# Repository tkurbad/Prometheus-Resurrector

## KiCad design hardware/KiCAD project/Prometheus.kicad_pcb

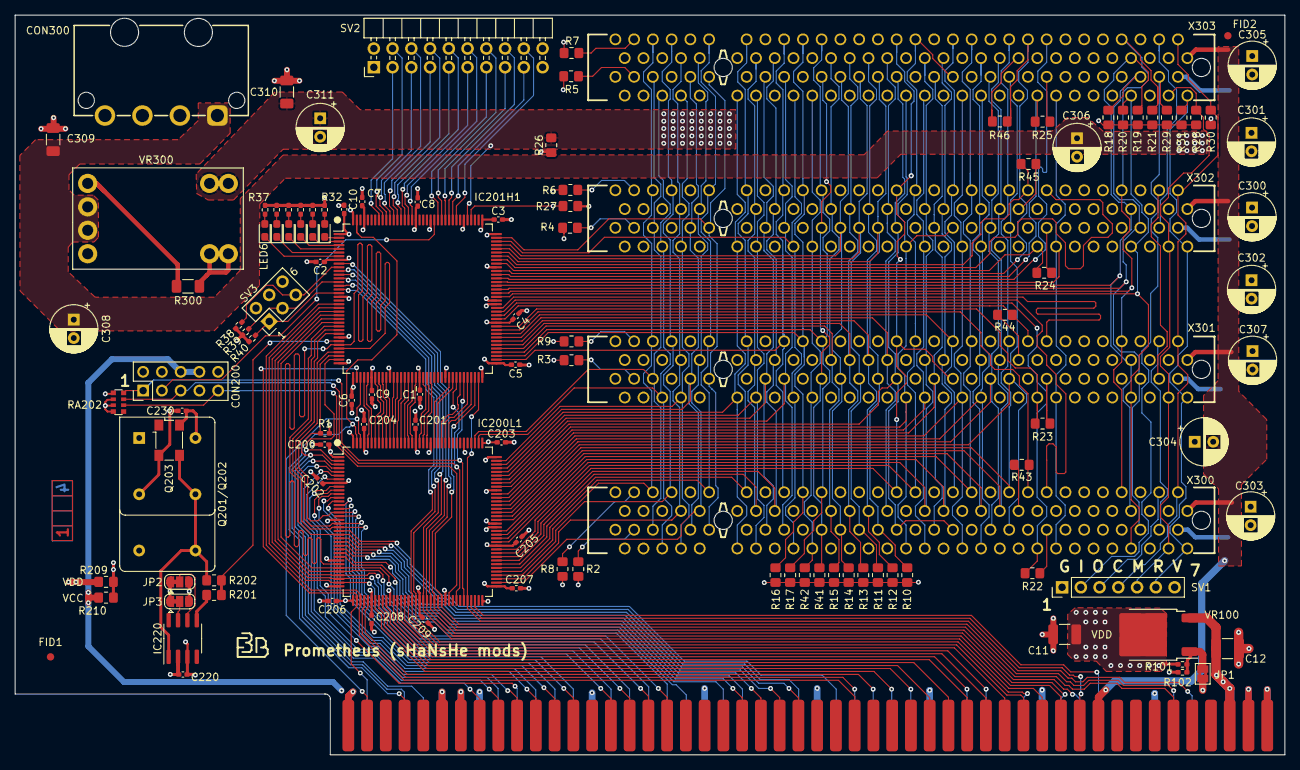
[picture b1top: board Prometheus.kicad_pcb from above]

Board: 4 copper layers, 172.0 x 100.2 mm, 118 parts (0 on the bottom side), 208 nets.

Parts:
C1, C2, C3, C4, C5, C6, C7, C8, C9, C10, C200, C201, C202, C203, C204, C205, C206, C207, C208, C209, C220, C230: 100nF; C_0402_1005Metric_Pad0.74x0.62mm_HandSolder
C11, C12: 10uF Tantalum; C_1210_3225Metric_Pad1.33x2.70mm_HandSolder
C300, C301, C302, C303, C304, C305, C306, C307, C308, C311: 100uF; CP_Radial_D6.3mm_P2.50mm
C309, C310: 100nF; C_1206_3216Metric_Pad1.33x1.80mm_HandSolder
CON200: Conn_02x05_Odd_Even; PinHeader_2x05_P2.54mm_Vertical
CON300: Conn_01x04_Pin; TE-350211-MATE-N-LCK-RightAngle
FID1, FID2: Fiducial; Fiducial_1mm_Mask2mm
IC200L1, IC201H1: XC95144XL-TQ144; TQFP-144_20x20mm_P0.5mm
IC220: NB3N502; SOIC-8_3.9x4.9mm_P1.27mm
JP1: SolderJumper_2_Bridged; SolderJumper-2_P1.3mm_Bridged2Bar_Pad1.0x1.5mm
JP2, JP3: SolderJumper_3_Bridged12; SolderJumper-3_P1.3mm_Bridged12_RoundedPad1.0x1.5mm
LED1, LED2, LED3, LED4, LED5, LED6: LED; LED_0603_1608Metric_Pad1.05x0.95mm_HandSolder
Q201/Q202: 33MHz; Oscillator_DIP-14_DIP-8
Q203: 33MHz; Oscillator_SMD_Fordahl_DFAS15-4Pin_5.0x3.2mm
R1, R38, R39, R40: 4k7; R_0402_1005Metric_Pad0.72x0.64mm_HandSolder
R2, R3, R4, R5, R6, R7, R8, R9, R10, R11, R12, R13, R14, R15, R16, R17, R18, R19, R20, R21, R22, R23, R24, R25, R28, R29, R30, R31, R41, R42: 1k0; R_0805_2012Metric_Pad1.20x1.40mm_HandSolder
R26: 3k3; R_0805_2012Metric_Pad1.20x1.40mm_HandSolder
R27: 4k7; R_0805_2012Metric_Pad1.20x1.40mm_HandSolder
R32, R33, R34, R35, R36, R37: 680; R_0402_1005Metric_Pad0.72x0.64mm_HandSolder
R43, R44, R45, R46: 10k0; R_0805_2012Metric_Pad1.20x1.40mm_HandSolder
R101: 150; R_0402_1005Metric_Pad0.72x0.64mm_HandSolder
R102: 240; R_0402_1005Metric_Pad0.72x0.64mm_HandSolder
R201, R202: 15R; R_0805_2012Metric_Pad1.20x1.40mm_HandSolder
R209, R210: FerriteBead_Small; R_0805_2012Metric_Pad1.20x1.40mm_HandSolder
R300: 2k0; R_1206_3216Metric_Pad1.30x1.75mm_HandSolder
RA202: R_Pack04; R_Array_Convex_4x0612
SV1: Conn_01x07_Pin; PinHeader_1x07_P2.54mm_Vertical
SV2: Conn_02x10_Odd_Even; PinHeader_2x10_P2.54mm_Horizontal
SV3: Conn_02x03_Odd_Even; PinHeader_2x03_P2.54mm_Vertical
U1: Zorro3
VR100: AP1117-ADJ; TO-252-2
VR300: DCDC
X300, X301, X302, X303: Bus_PCI_32bit_5V; PCI

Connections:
+3V3: C310.1, C311.1, IC201H1.113, R26.2, VR300.6 (VOUT), X300.A21 (+3.3V), X300.A27 (+3.3V), X300.A33 (+3.3V), X300.A39 (+3.3V), X300.A45 (+3.3V), X300.A53 (+3.3V), X300.B25 (+3.3V), X300.B31 (+3.3V), X300.B36 (+3.3V), X300.B41 (+3.3V), X300.B43 (+3.3V), X300.B54 (+3.3V), X301.A21 (+3.3V), X301.A27 (+3.3V), X301.A33 (+3.3V), X301.A39 (+3.3V), X301.A45 (+3.3V), X301.A53 (+3.3V), X301.B25 (+3.3V), X301.B31 (+3.3V), X301.B36 (+3.3V), X301.B41 (+3.3V), X301.B43 (+3.3V), X301.B54 (+3.3V), X302.A21 (+3.3V), X302.A27 (+3.3V), X302.A33 (+3.3V), X302.A39 (+3.3V), X302.A45 (+3.3V), X302.A53 (+3.3V), X302.B25 (+3.3V), X302.B31 (+3.3V), X302.B36 (+3.3V), X302.B41 (+3.3V), X302.B43 (+3.3V), X302.B54 (+3.3V), X303.A21 (+3.3V), X303.A27 (+3.3V), X303.A33 (+3.3V), X303.A39 (+3.3V), X303.A45 (+3.3V), X303.A53 (+3.3V), X303.B25 (+3.3V), X303.B31 (+3.3V), X303.B36 (+3.3V), X303.B41 (+3.3V), X303.B43 (+3.3V), X303.B54 (+3.3V)
+5V: C300.1, C303.1, C305.1, C307.1, CON300.4, IC201H1.112, R2.1, R3.1, R4.1, R5.1, R6.2, R7.2, R8.2, R9.2, R10.2, R11.2, R12.2, R13.2, R14.2, R15.2, R16.2, R17.2, R18.2, R19.2, R20.2, R21.2, R22.2, R23.2, R24.2, R25.2, R27.2, R28.2, R29.2, R31.2, R41.2, R42.2, R43.2, R44.2, R45.2, R46.2, SV1.7, X300.A5 (+5V), X300.A8 (+5V), X300.A10 (+5V), X300.A16 (+5V), X300.A59 (+5V), X300.A61 (+5V), X300.A62 (+5V), X300.B5 (+5V), X300.B6 (+5V), X300.B19 (+5V), X300.B59 (+5V), X300.B61 (+5V), X300.B62 (+5V), X301.A5 (+5V), X301.A8 (+5V), X301.A10 (+5V), X301.A16 (+5V), X301.A59 (+5V), X301.A61 (+5V), X301.A62 (+5V), X301.B5 (+5V), X301.B6 (+5V), X301.B19 (+5V), X301.B59 (+5V), X301.B61 (+5V), X301.B62 (+5V), X302.A5 (+5V), X302.A8 (+5V), X302.A10 (+5V), X302.A16 (+5V), X302.A59 (+5V), X302.A61 (+5V), X302.A62 (+5V), X302.B5 (+5V), X302.B6 (+5V), X302.B19 (+5V), X302.B59 (+5V), X302.B61 (+5V), X302.B62 (+5V), X303.A5 (+5V), X303.A8 (+5V), X303.A10 (+5V), X303.A16 (+5V), X303.A59 (+5V), X303.A61 (+5V), X303.A62 (+5V), X303.B5 (+5V), X303.B6 (+5V), X303.B19 (+5V), X303.B59 (+5V), X303.B61 (+5V), X303.B62 (+5V)
+12V: C301.1, C302.1, C306.1, C308.1, C309.1, CON300.1, VR300.2 (TRACK), VR300.3 (VIN), X300.A2 (+12V), X301.A2 (+12V), X302.A2 (+12V), X303.A2 (+12V)
-12V: C304.2, U1.20 (-12VDC), X300.B1 (-12V), X301.B1 (-12V), X302.B1 (-12V), X303.B1 (-12V)
AD8: IC200L1.52, U1.30 (AD8)
AD9: IC200L1.50, U1.32 (AD9)
AD10: IC200L1.48, U1.34 (AD10)
AD11: IC200L1.46, U1.36 (AD11)
AD12: IC200L1.45, U1.38 (AD12)
AD13: IC200L1.44, U1.39 (AD13)
AD14: IC200L1.43, U1.41 (AD14)
AD15: IC200L1.41, U1.43 (AD15)
AD16: IC200L1.40, U1.45 (AD16)
AD17: IC200L1.21, U1.47 (AD17)
AD18: IC200L1.23, U1.52 (AD18)
AD19: IC200L1.24, U1.54 (AD19)
AD20: IC200L1.25, U1.56 (AD20)
AD21: IC200L1.27, U1.58 (AD21)
AD22: IC200L1.26, U1.57 (AD22)
AD23: IC200L1.28, U1.59 (AD23)
AD24: IC200L1.10, U1.80 (AD24)
AD25: IC200L1.12, U1.78 (AD25)
AD26: IC200L1.14, U1.76 (AD26)
AD27: IC200L1.17, U1.71 (AD27)
AD28: IC200L1.20, IC201H1.27, U1.69 (AD28)
AD29: IC200L1.34, IC201H1.22, U1.67 (AD29)
AD30: IC200L1.32 (I/O/GCK2), IC201H1.24, U1.65 (AD30)
AD31: IC200L1.31, IC201H1.25, U1.63 (AD31)
DEBUG0: IC201H1.116, SV2.18
DEBUG1: IC201H1.117, SV2.17
DEBUG2: IC201H1.118, SV2.16
DEBUG3: IC201H1.119, SV2.15
DEBUG4: IC201H1.120, SV2.14
DEBUG5: IC201H1.121, SV2.13
DEBUG6: IC201H1.128, SV2.12
DEBUG7: IC201H1.129, SV2.11
DEBUG8: IC201H1.130, SV2.10
DEBUG9: IC201H1.131, SV2.9
DEBUG10: IC201H1.132, SV2.8
DEBUG11: IC201H1.133, SV2.7
DEBUG12: IC201H1.134, SV2.6
DEBUG13: IC201H1.135, SV2.5
DEBUG14: IC201H1.136, SV2.4
DEBUG15: IC201H1.137, SV2.3
DOE: IC200L1.2 (I/O/GTS3), IC201H1.35, U1.93 (DOE)
FC0: IC200L1.51, U1.31 (FC0)
FC1: IC200L1.49, U1.33 (FC1)
GNDD: C1.2, C2.2, C3.2, C4.2, C5.2, C6.2, C7.2, C8.2, C9.2, C10.2, C11.2, C12.2, C200.2, C201.2, C202.2, C203.2, C204.2, C205.2, C206.2, C207.2, C208.2, C209.2, C220.2, C230.2, C300.2, C301.2, C302.2, C303.2, C304.1, C305.2, C306.2, C307.2, C308.2, C309.2, C310.2, C311.2, CON200.2, CON200.10, CON300.2, CON300.3, IC200L1.18 (GND), IC200L1.29 (GND), IC200L1.36 (GND), IC200L1.47 (GND), IC200L1.62 (GND), IC200L1.72 (GND), IC200L1.89 (GND), IC200L1.90 (GND), IC200L1.99 (GND), IC200L1.108 (GND), IC200L1.114 (GND), IC200L1.123 (GND), IC200L1.144 (GND), IC201H1.18 (GND), IC201H1.29 (GND), IC201H1.36 (GND), IC201H1.47 (GND), IC201H1.62 (GND), IC201H1.72 (GND), IC201H1.89 (GND), IC201H1.90 (GND), IC201H1.99 (GND), IC201H1.108 (GND), IC201H1.114 (GND), IC201H1.123 (GND), IC201H1.144 (GND), IC220.3 (GND), JP1.2 (B), JP2.1 (A), JP3.1 (A), Q201/Q202.4 (GND), Q201/Q202.7 (GND), Q203.2 (GND), R26.1, R27.1, R30.2, R102.2, R300.1, RA202.1 (R1.1), SV1.1, SV2.1, SV2.2, SV2.19, SV2.20, SV3.2, SV3.4, SV3.6, U1.1 (GND), U1.2 (GND), U1.3 (GND), U1.4 (GND), U1.13 (GND), U1.25 (GND), U1.37 (GND), U1.49 (GND), U1.61 (GND), U1.73 (GND), U1.85 (GND), U1.87 (GND), U1.88 (GND), U1.89 (GND), U1.90 (GND), U1.99 (GND), U1.100 (GND), VR300.1 (GND), X300.A12 (GND), X300.A13 (GND), X300.A18 (GND), X300.A24 (GND), X300.A30 (GND), X300.A35 (GND), X300.A37 (GND), X300.A42 (GND), X300.A48 (GND), X300.A56 (GND), X300.B3 (GND), X300.B12 (GND), X300.B13 (GND), X300.B15 (GND), X300.B17 (GND), X300.B22 (GND), X300.B28 (GND), X300.B34 (GND), X300.B38 (GND), X300.B46 (GND), X300.B49 (GND), X300.B57 (GND), X301.A12 (GND), X301.A13 (GND), X301.A18 (GND), X301.A24 (GND), X301.A30 (GND), X301.A35 (GND), X301.A37 (GND), X301.A42 (GND), X301.A48 (GND), X301.A56 (GND), X301.B3 (GND), X301.B12 (GND), X301.B13 (GND), X301.B15 (GND), X301.B17 (GND), X301.B22 (GND), X301.B28 (GND), X301.B34 (GND), X301.B38 (GND), X301.B46 (GND), X301.B49 (GND), X301.B57 (GND), X302.A12 (GND), X302.A13 (GND), X302.A18 (GND), X302.A24 (GND), X302.A30 (GND), X302.A35 (GND), X302.A37 (GND), X302.A42 (GND), X302.A48 (GND), X302.A56 (GND), X302.B3 (GND), X302.B12 (GND), X302.B13 (GND), X302.B15 (GND), X302.B17 (GND), X302.B22 (GND), X302.B28 (GND), X302.B34 (GND), X302.B38 (GND), X302.B46 (GND), X302.B49 (GND), X302.B57 (GND), X303.A12 (GND), X303.A13 (GND), X303.A18 (GND), X303.A24 (GND), X303.A30 (GND), X303.A35 (GND), X303.A37 (GND), X303.A42 (GND), X303.A48 (GND), X303.A56 (GND), X303.B3 (GND), X303.B12 (GND), X303.B13 (GND), X303.B15 (GND), X303.B17 (GND), X303.B22 (GND), X303.B28 (GND), X303.B34 (GND), X303.B38 (GND), X303.B46 (GND), X303.B49 (GND), X303.B57 (GND)
ICON0: IC200L1.140, IC201H1.40
ICON1: IC200L1.139, IC201H1.41
ICON2: IC200L1.138, IC201H1.43
ICON3: IC200L1.137, IC201H1.44
ICON4: IC200L1.136, IC201H1.45
ICON5: IC200L1.135, IC201H1.46
ICON6: IC200L1.134, IC201H1.48
ICON7: IC200L1.133, IC201H1.49
ICON8: IC200L1.132, IC201H1.50
ICON9: IC200L1.131, IC201H1.51
ICON10: IC200L1.130, IC201H1.52
ICON11: IC200L1.129, IC201H1.53
ICON12: IC200L1.128, IC201H1.54
ICON13: IC200L1.126, IC201H1.56
ICON14: IC200L1.125, IC201H1.57
ICON15: IC200L1.124, IC201H1.58
ICON16: IC200L1.121, IC201H1.64
ICON17: IC200L1.120, IC201H1.66
ICON18: IC200L1.119, IC201H1.68
ICON19: IC200L1.118, IC201H1.69
LED0: IC201H1.2 (I/O/GTS3), LED1.1 (K)
LED1: IC201H1.3 (I/O/GTS4), LED2.1 (K)
LED2: IC201H1.4, LED3.1 (K)
LED3: IC201H1.5 (I/O/GTS1), LED4.1 (K)
LED4: IC201H1.6 (I/O/GTS2), LED5.1 (K)
LED5: IC201H1.7, LED6.1 (K)
MASTERCLK: IC200L1.30 (I/O/GCK1), IC201H1.31, IC201H1.32 (I/O/GCK2)
unnamed: IC220.6 (S0), JP2.2 (C)
unnamed: IC220.7 (S1), JP3.2 (C)
unnamed: JP1.1 (A), R101.2, R102.1, VR100.1 (ADJ)
unnamed: LED1.2 (A), R32.1
unnamed: LED2.2 (A), R33.1
unnamed: LED3.2 (A), R34.1
unnamed: LED4.2 (A), R35.1
unnamed: LED5.2 (A), R36.1
unnamed: LED6.2 (A), R37.1
unnamed: R300.2, VR300.5 (VADJ)
unnamed: R8.1, X300.B60 (ACK64#)
unnamed: R2.2, X300.A60 (REQ64#)
unnamed: R9.1, X301.B60 (ACK64#)
unnamed: R3.2, X301.A60 (REQ64#)
unnamed: R6.1, X302.B60 (ACK64#)
unnamed: R4.2, X302.A60 (REQ64#)
unnamed: R7.1, X303.B60 (ACK64#)
unnamed: R5.2, X303.A60 (REQ64#)
OPT0: IC201H1.10, R38.1, SV3.5
OPT1: IC201H1.14, R39.1, SV3.3
OPT2: IC201H1.17, R40.1, SV3.1
P-AD0: IC200L1.111, X300.A58 (AD[00]), X301.A58 (AD[00]), X302.A58 (AD[00]), X303.A58 (AD[00])
P-AD1: IC200L1.77, X300.B58 (AD[01]), X301.B58 (AD[01]), X302.B58 (AD[01]), X303.B58 (AD[01])
P-AD2: IC200L1.110, X300.A57 (AD[02]), X301.A57 (AD[02]), X302.A57 (AD[02]), X303.A57 (AD[02])
P-AD3: IC200L1.76, X300.B56 (AD[03]), X301.B56 (AD[03]), X302.B56 (AD[03]), X303.B56 (AD[03])
P-AD4: IC200L1.107, X300.A55 (AD[04]), X301.A55 (AD[04]), X302.A55 (AD[04]), X303.A55 (AD[04])
P-AD5: IC200L1.75, X300.B55 (AD[05]), X301.B55 (AD[05]), X302.B55 (AD[05]), X303.B55 (AD[05])
P-AD6: IC200L1.106, X300.A54 (AD[06]), X301.A54 (AD[06]), X302.A54 (AD[06]), X303.A54 (AD[06])
P-AD7: IC200L1.74, X300.B53 (AD[07]), X301.B53 (AD[07]), X302.B53 (AD[07]), X303.B53 (AD[07])
P-AD8: IC200L1.78, X300.B52 (AD[08]), X301.B52 (AD[08]), X302.B52 (AD[08]), X303.B52 (AD[08])
P-AD9: IC200L1.105, X300.A49 (AD[09]), X301.A49 (AD[09]), X302.A49 (AD[09]), X303.A49 (AD[09])
P-AD10: IC200L1.79, X300.B48 (AD[10]), X301.B48 (AD[10]), X302.B48 (AD[10]), X303.B48 (AD[10])
P-AD11: IC200L1.104, X300.A47 (AD[11]), X301.A47 (AD[11]), X302.A47 (AD[11]), X303.A47 (AD[11])
P-AD12: IC200L1.80, X300.B47 (AD[12]), X301.B47 (AD[12]), X302.B47 (AD[12]), X303.B47 (AD[12])
P-AD13: IC200L1.103, X300.A46 (AD[13]), X301.A46 (AD[13]), X302.A46 (AD[13]), X303.A46 (AD[13])
P-AD14: IC200L1.81, X300.B45 (AD[14]), X301.B45 (AD[14]), X302.B45 (AD[14]), X303.B45 (AD[14])
P-AD15: IC200L1.102, X300.A44 (AD[15]), X301.A44 (AD[15]), X302.A44 (AD[15]), X303.A44 (AD[15])
P-AD16: IC200L1.101, X300.A26 (IDSEL), X300.A32 (AD[16]), X301.A32 (AD[16]), X302.A32 (AD[16]), X303.A32 (AD[16])
P-AD17: IC200L1.82, X300.B32 (AD[17]), X301.A26 (IDSEL), X301.B32 (AD[17]), X302.B32 (AD[17]), X303.B32 (AD[17])
P-AD18: IC200L1.100, X300.A31 (AD[18]), X301.A31 (AD[18]), X302.A26 (IDSEL), X302.A31 (AD[18]), X303.A31 (AD[18])
P-AD19: IC200L1.83, X300.B30 (AD[19]), X301.B30 (AD[19]), X302.B30 (AD[19]), X303.A26 (IDSEL), X303.B30 (AD[19])
P-AD20: IC200L1.98, X300.A29 (AD[20]), X301.A29 (AD[20]), X302.A29 (AD[20]), X303.A29 (AD[20])
P-AD21: IC200L1.85, X300.B29 (AD[21]), X301.B29 (AD[21]), X302.B29 (AD[21]), X303.B29 (AD[21])
P-AD22: IC200L1.97, X300.A28 (AD[22]), X301.A28 (AD[22]), X302.A28 (AD[22]), X303.A28 (AD[22])
P-AD23: IC200L1.86, X300.B27 (AD[23]), X301.B27 (AD[23]), X302.B27 (AD[23]), X303.B27 (AD[23])
P-AD24: IC200L1.96, X300.A25 (AD[24]), X301.A25 (AD[24]), X302.A25 (AD[24]), X303.A25 (AD[24])
P-AD25: IC200L1.87, X300.B24 (AD[25]), X301.B24 (AD[25]), X302.B24 (AD[25]), X303.B24 (AD[25])
P-AD26: IC200L1.95, X300.A23 (AD[26]), X301.A23 (AD[26]), X302.A23 (AD[26]), X303.A23 (AD[26])
P-AD27: IC200L1.88, X300.B23 (AD[27]), X301.B23 (AD[27]), X302.B23 (AD[27]), X303.B23 (AD[27])
P-AD28: IC200L1.94, X300.A22 (AD[28]), X301.A22 (AD[28]), X302.A22 (AD[28]), X303.A22 (AD[28])
P-AD29: IC200L1.91, X300.B21 (AD[29]), X301.B21 (AD[29]), X302.B21 (AD[29]), X303.B21 (AD[29])
P-AD30: IC200L1.93, X300.A20 (AD[30]), X301.A20 (AD[30]), X302.A20 (AD[30]), X303.A20 (AD[30])
P-AD31: IC200L1.92, X300.B20 (AD[31]), X301.B20 (AD[31]), X302.B20 (AD[31]), X303.B20 (AD[31])
P-CLK0: IC201H1.87, X300.B16 (CLK)
P-CLK1: IC201H1.88, X301.B16 (CLK)
P-CLK2: IC201H1.101, X302.B16 (CLK)
P-CLK3: IC201H1.96, X303.B16 (CLK)
P-PAR: IC201H1.106, X300.A43 (PAR), X301.A43 (PAR), X302.A43 (PAR), X303.A43 (PAR)
P-TCK: R30.1, SV1.4, X300.B2 (TCK), X301.B2 (TCK), X302.B2 (TCK), X303.B2 (TCK)
P-TD1: X302.A4 (TDI), X303.B4 (TDO)
P-TD2: X301.A4 (TDI), X302.B4 (TDO)
P-TD3: X300.A4 (TDI), X301.B4 (TDO)
P-TDI: R29.1, SV1.2, X303.A4 (TDI)
P-TDO: SV1.3, X300.B4 (TDO)
P-TMS: R28.1, SV1.5, X300.A3 (TMS), X301.A3 (TMS), X302.A3 (TMS), X303.A3 (TMS)
P-TRST: R31.1, SV1.6, X300.A1 (TRST#), X301.A1 (TRST#), X302.A1 (TRST#), X303.A1 (TRST#)
READ: IC200L1.35, IC201H1.21, U1.68 (READ)
SA2: IC200L1.54, IC201H1.15, U1.27 (A2)
SA3: IC200L1.56, IC201H1.13, U1.26 (A3)
SA4: IC200L1.57, IC201H1.12, U1.24 (A4)
SA5: IC200L1.59, IC201H1.9, U1.21 (A5)
SA6: IC200L1.58, IC201H1.11, U1.23 (A6)
SA7: IC200L1.53, IC201H1.16, U1.28 (A7)
SD0: IC200L1.15, U1.75 (SD0)
SD1: IC200L1.13, U1.77 (SD1)
SD2: IC200L1.11, U1.79 (SD2)
SD3: IC200L1.9, U1.81 (SD3)
SD4: IC200L1.6 (I/O/GTS2), U1.83 (SD4)
SD5: IC200L1.4, U1.86 (SD5)
SD6: IC200L1.5 (I/O/GTS1), U1.84 (SD6)
SD7: IC200L1.7, U1.82 (SD7)
SDONE: R41.1, X300.A40 (SDONE), X301.A40 (SDONE), X302.A40 (SDONE), X303.A40 (SDONE)
SENSEZ3: IC200L1.3 (I/O/GTS4), IC201H1.34, R1.2, U1.91 (SENSEZ3)
SYSCLK: IC201H1.30 (I/O/GCK1), R201.2, R202.2
SYSCLK_OSC: IC220.1 (X1/CLK), Q201/Q202.8 (OUT), Q201/Q202.11 (OUT), Q203.3 (OUT), R202.1
SYSCLK_PLL: IC220.5 (CLKOUT), R201.1
TCK: CON200.1, IC200L1.67 (TCK), IC201H1.67 (TCK), RA202.8 (R1.2)
TDI: CON200.9, IC200L1.63 (TDI), RA202.6 (R3.2)
TDO: CON200.3, IC201H1.122 (TDO)
TDO-TDI: IC200L1.122 (TDO), IC201H1.63 (TDI)
TMS: CON200.5, IC200L1.65 (TMS), IC201H1.65 (TMS), RA202.7 (R2.2)
VCC: C12.1, CON200.6, CON200.8, R210.1, U1.5 (+5VDC), U1.6 (+5VDC), VR100.3 (VI)
VDD: C1.1, C2.1, C3.1, C4.1, C5.1, C6.1, C7.1, C8.1, C9.1, C10.1, C11.1, C200.1, C201.1, C202.1, C203.1, C204.1, C205.1, C206.1, C207.1, C208.1, C209.1, CON200.4, IC200L1.1 (VCCIO), IC200L1.8 (VCCINT), IC200L1.37 (VCCIO), IC200L1.42 (VCCINT), IC200L1.55 (VCCIO), IC200L1.73 (VCCIO), IC200L1.84 (VCCINT), IC200L1.109 (VCCIO), IC200L1.127 (VCCIO), IC200L1.141 (VCCINT), IC201H1.1 (VCCIO), IC201H1.8 (VCCINT), IC201H1.37 (VCCIO), IC201H1.42 (VCCINT), IC201H1.55 (VCCIO), IC201H1.73 (VCCIO), IC201H1.84 (VCCINT), IC201H1.109 (VCCIO), IC201H1.127 (VCCIO), IC201H1.141 (VCCINT), R1.1, R32.2, R33.2, R34.2, R35.2, R36.2, R37.2, R38.2, R39.2, R40.2, R101.1, R209.1, RA202.2 (R2.1), RA202.3 (R3.1), RA202.4 (R4.1), VR100.2 (VO)
VPP: C220.1, C230.1, IC220.2 (VDD), JP2.3 (B), JP3.3 (B), Q201/Q202.14 (Vcc), Q203.4 (V+), R209.2, R210.2
~BERR: IC200L1.39, IC201H1.20, U1.46 (~BERR)
~CFGIN: IC200L1.60, U1.12 (~CFGINN)
~CFGOUT: IC200L1.61, IC201H1.70, U1.11 (~CFGOUTN)
~DS0: IC200L1.22, IC201H1.26, U1.51 (~DS0)
~DS1: IC200L1.142, IC201H1.39, U1.98 (~DS1)
~DS2: IC200L1.19, IC201H1.28, U1.70 (~DS2)
~DS3: IC200L1.16, IC201H1.33, U1.72 (~DS3)
~DTACK: IC200L1.33, IC201H1.23, U1.66 (~DTACK)
~FCS: IC200L1.38 (I/O/GCK3), IC201H1.38 (I/O/GCK3), U1.97 (~FCS)
~INT2: IC200L1.70, U1.19 (~INT2)
~INT6: IC200L1.69, U1.22 (~INT6)
~IORST: IC200L1.143 (I/O/GSR), IC201H1.143 (I/O/GSR), U1.94 (~IORST)
~P-CBE0: IC201H1.107, X300.A52 (C/BE#[0]), X301.A52 (C/BE#[0]), X302.A52 (C/BE#[0]), X303.A52 (C/BE#[0])
~P-CBE1: IC201H1.74, X300.B44 (C/BE#[1]), X301.B44 (C/BE#[1]), X302.B44 (C/BE#[1]), X303.B44 (C/BE#[1])
~P-CBE2: IC201H1.80, X300.B33 (C/BE#[2]), X301.B33 (C/BE#[2]), X302.B33 (C/BE#[2]), X303.B33 (C/BE#[2])
~P-CBE3: IC201H1.81, X300.B26 (C/BE#[3]), X301.B26 (C/BE#[3]), X302.B26 (C/BE#[3]), X303.B26 (C/BE#[3])
~P-DEVSEL: IC201H1.78, R13.1, X300.B37 (DEVSEL#), X301.B37 (DEVSEL#), X302.B37 (DEVSEL#), X303.B37 (DEVSEL#)
~P-FRAME: IC201H1.103, R10.1, X300.A34 (FRAME#), X301.A34 (FRAME#), X302.A34 (FRAME#), X303.A34 (FRAME#)
~P-GNT0: IC201H1.86, R22.1, X300.A17 (GNT#)
~P-GNT1: IC201H1.83, R23.1, X301.A17 (GNT#)
~P-GNT2: IC201H1.100, R24.1, X302.A17 (GNT#)
~P-GNT3: IC201H1.97, R25.1, X303.A17 (GNT#)
~P-INTA: IC201H1.93, R18.1, X300.A6 (INTA#), X301.A6 (INTA#), X302.A6 (INTA#), X303.A6 (INTA#)
~P-INTB: IC201H1.94, R19.1, X300.B7 (INTB#), X301.B7 (INTB#), X302.B7 (INTB#), X303.B7 (INTB#)
~P-INTC: IC201H1.91, R20.1, X300.A7 (INTC#), X301.A7 (INTC#), X302.A7 (INTC#), X303.A7 (INTC#)
~P-INTD: IC201H1.92, R21.1, X300.B8 (INTD#), X301.B8 (INTD#), X302.B8 (INTD#), X303.B8 (INTD#)
~P-IRDY: IC201H1.79, R12.1, X300.B35 (IRDY#), X301.B35 (IRDY#), X302.B35 (IRDY#), X303.B35 (IRDY#)
~P-LOCK: IC201H1.77, R15.1, X300.B39 (LOCK#), X301.B39 (LOCK#), X302.B39 (LOCK#), X303.B39 (LOCK#)
~P-PERR: IC201H1.76, R17.1, X300.B40 (PERR#), X301.B40 (PERR#), X302.B40 (PERR#), X303.B40 (PERR#)
~P-REQ0: IC201H1.82, R43.1, X300.B18 (REQ#)
~P-REQ1: IC201H1.85, R44.1, X301.B18 (REQ#)
~P-REQ2: IC201H1.102, R45.1, X302.B18 (REQ#)
~P-REQ3: IC201H1.98, R46.1, X303.B18 (REQ#)
~P-RST: IC201H1.95, X300.A15 (RST#), X301.A15 (RST#), X302.A15 (RST#), X303.A15 (RST#)
~P-SERR: IC201H1.75, R16.1, X300.B42 (SERR#), X301.B42 (SERR#), X302.B42 (SERR#), X303.B42 (SERR#)
~P-STOP: IC201H1.105, R14.1, X300.A38 (STOP#), X301.A38 (STOP#), X302.A38 (STOP#), X303.A38 (STOP#)
~P-TRDY: IC201H1.104, R11.1, X300.A36 (TRDY#), X301.A36 (TRDY#), X302.A36 (TRDY#), X303.A36 (TRDY#)
~SBO: R42.1, X300.A41 (SBO#), X301.A41 (SBO#), X302.A41 (SBO#), X303.A41 (SBO#)
~SLAVEN: IC200L1.68, IC201H1.71, U1.9 (~SLAVEN)

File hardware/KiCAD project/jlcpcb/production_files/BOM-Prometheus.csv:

Comment,Designator,Footprint,LCSC
R_Pack04,RA202,R_Array_Convex_4x0612,C102645
3k3,R26,R_0805_2012Metric_Pad1.20x1.40mm_HandSolder,C104228
4k7,R27,R_0805_2012Metric_Pad1.20x1.40mm_HandSolder,C104344
1k0,"R10,R11,R12,R13,R14,R15,R16,R17,R18,R19,R2,R20,R21,R22,R23,R24,R25,R28,R29,R3,R30,R31,R4,R41,R42,R5,R6,R7,R8,R9",R_0805_2012Metric_Pad1.20x1.40mm_HandSolder,C17513
LED,"LED1,LED2,LED3,LED4,LED5,LED6",LED_0603_1608Metric_Pad1.05x0.95mm_HandSolder,C205448
100nF,"C309,C310",C_1206_3216Metric_Pad1.33x1.80mm_HandSolder,C24497
680,"R32,R33,R34,R35,R36,R37",R_0402_1005Metric_Pad0.72x0.64mm_HandSolder,C25130
4k7,"R1,R38,R39,R40",R_0402_1005Metric_Pad0.72x0.64mm_HandSolder,C2906869
15R,R202,R_0805_2012Metric_Pad1.20x1.40mm_HandSolder,C2907229
10k0,"R43,R44,R45,R46",R_0805_2012Metric_Pad1.20x1.40mm_HandSolder,C3016734
FerriteBead_Small,R209,R_0805_2012Metric_Pad1.20x1.40mm_HandSolder,C304328
100nF,"C1,C10,C2,C200,C201,C202,C203,C204,C205,C206,C207,C208,C209,C220,C230,C3,C4,C5,C6,C7,C8,C9",C_0402_1005Metric_Pad0.74x0.62mm_HandSolder,C307331
AP1117-ADJ,VR100,TO-252-2,C347249
33MHz,Q203,Oscillator_SMD_Fordahl_DFAS15-4Pin_5.0x3.2mm,C387073
10uF Tantalum,"C11,C12",C_1210_3225Metric_Pad1.33x2.70mm_HandSolder,C4988312
2k0,R300,R_1206_3216Metric_Pad1.30x1.75mm_HandSolder,C844428
100uF,C303,CP_Radial_D6.3mm_P2.50mm,
100uF,C308,CP_Radial_D6.3mm_P2.50mm,
100uF,C311,CP_Radial_D6.3mm_P2.50mm,
100uF,C305,CP_Radial_D6.3mm_P2.50mm,
100uF,C307,CP_Radial_D6.3mm_P2.50mm,
100uF,C300,CP_Radial_D6.3mm_P2.50mm,
100uF,C302,CP_Radial_D6.3mm_P2.50mm,
100uF,C304,CP_Radial_D6.3mm_P2.50mm,
100uF,C306,CP_Radial_D6.3mm_P2.50mm,
XC95144XL-TQ144,IC201H1,TQFP-144_20x20mm_P0.5mm,
100uF,C301,CP_Radial_D6.3mm_P2.50mm,
XC95144XL-TQ144,IC200L1,TQFP-144_20x20mm_P0.5mm,

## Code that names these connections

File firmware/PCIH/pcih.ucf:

# PROTOTYPE

# Clock period
#NET "SYSCLK" PERIOD = 15;

# Pin assignment
#NET "LED<0>"		LOC = "P2";
#NET "LED<1>"		LOC = "P3";
#NET "LED<2>"		LOC = "P4";
#NET "LED<3>"		LOC = "P5";
#NET "LED<4>"		LOC = "P6";
#NET "LED<5>"		LOC = "P7";
NET "Z_AA<5>"		LOC = "P9";
#NET "OPT<0>"		LOC = "P10";
NET "Z_AA<6>"		LOC = "P11";
NET "Z_AA<4>"		LOC = "P12";
NET "Z_AA<3>"		LOC = "P13";
#NET "OPT<1>"		LOC = "P14";
NET "Z_AA<2>"		LOC = "P15";
NET "Z_AA<7>"		LOC = "P16";
#NET "OPT<2>"		LOC = "P17";
#NET ""				LOC = "P19"; # NOTUSED19H 
NET "Z_NBERR"		LOC = "P20";
NET "Z_READ"		LOC = "P21";
NET "Z_ADA<29>"	LOC = "P22";
NET "Z_NDTACK"		LOC = "P23";
NET "Z_ADA<30>"	LOC = "P24";
NET "Z_ADA<31>"	LOC = "P25";
NET "Z_NDS<0>"		LOC = "P26";
NET "Z_ADA<28>"	LOC = "P27";
NET "Z_NDS<2>"		LOC = "P28";
NET "I_33M"			LOC = "P30"; # master clock in
NET "I_PCICLK"		LOC = "P31"; # out
NET "I_PCICLK2"	LOC = "P32"; # in 
NET "Z_NDS<3>"		LOC = "P33";
NET "Z_Z3SENSE"	LOC = "P34";
NET "Z_DOE"			LOC = "P35";
NET "Z_NFCS"		LOC = "P38";
NET "Z_NDS<1>"		LOC = "P39";
NET "I_ACC<1>"		LOC = "P40"; # ICON0
NET "I_ACC<0>"		LOC = "P41"; # ICON1
NET "I_DATPAR<1>"	LOC = "P43"; # ICON2
NET "I_DATPAR<0>"	LOC = "P44"; # ICON3
NET "I_DAOUT"		LOC = "P45"; # ICON4
NET "I_PCIENA"		LOC = "P46"; # ICON5
NET "I_PCIDL"		LOC = "P48"; # ICON6
NET "I_DATA"		LOC = "P49"; # ICON7
NET "I_CFLT"		LOC = "P50"; # ICON8
NET "I_PLA<1>"		LOC = "P51"; # ICON9
NET "I_PLA<0>"		LOC = "P52"; # ICON10
NET "I_ZLA"			LOC = "P53"; # ICON11
NET "I_ZMA"			LOC = "P54"; # ICON12
#NET "I_ADD<0>"		LOC = "P56"; # ICON13
#NET "I_ADD<1>"		LOC = "P57"; # ICON14
#NET "I_ADD<2>"		LOC = "P58"; # ICON15
#NET ""				LOC = "P59"; # NOTUSED59H  
#NET ""				LOC = "P60"; # NOTUSED60H  
#NET ""				LOC = "P61"; # NOTUSED61H  
#NET "I_ADD<3>"		LOC = "P64"; # ICON16
#NET ""				LOC = "P66"; # ICON17
NET "I_NINT6"		LOC = "P68"; # ICON18
NET "I_NINT2"		LOC = "P69"; # ICON19
NET "Z_NCFGOUT"	LOC = "P70";
NET "Z_NSLAVE"		LOC = "P71";
NET "P_CBE<1>"		LOC = "P74";
NET "P_NSERR"		LOC = "P75";
NET "P_NPERR"		LOC = "P76";
NET "P_NLOCK"		LOC = "P77";
NET "P_NDEVSEL"	LOC = "P78";
NET "P_NIRDY"		LOC = "P79";
NET "P_CBE<2>"		LOC = "P80";
NET "P_CBE<3>"		LOC = "P81";
NET "P_NREQ<0>"	LOC = "P82";
NET "P_NGNT<1>"	LOC = "P83";
NET "P_NREQ<1>"	LOC = "P85";
NET "P_NGNT<0>"	LOC = "P86";
NET "P_CLKOUT<0>"	LOC = "P87";
NET "P_CLKOUT<1>"	LOC = "P88";
NET "P_NINTC"		LOC = "P91";
NET "P_NINTD"		LOC = "P92";
NET "P_NINTA"		LOC = "P93";
NET "P_NINTB"		LOC = "P94";
NET "P_NRESET"		LOC = "P95";
NET "P_CLKOUT<3>"	LOC = "P96";
NET "P_NGNT<3>"	LOC = "P97";
NET "P_NREQ<3>"	LOC = "P98";
NET "P_NGNT<2>"	LOC = "P100";
NET "P_CLKOUT<2>"	LOC = "P101";
NET "P_NREQ<2>"	LOC = "P102";
NET "P_NFRAME"		LOC = "P103";
NET "P_NTRDY"		LOC = "P104";
NET "P_NSTOP"		LOC = "P105";
NET "P_PAR"			LOC = "P106";
NET "P_CBE<0>"		LOC = "P107";
#NET ""				LOC = "P110"; # NOTUSED110H                       
#NET ""				LOC = "P111"; # NOTUSED111H
#NET "SENSE_5V0"	LOC = "P112";
#NET "SENSE_3V3"	LOC = "P113";
#NET ""				LOC = "P115"; # NOTUSED115H
NET "DEBUG<0>"		LOC = "P116";
NET "DEBUG<1>"		LOC = "P117";
NET "DEBUG<2>"		LOC = "P118";
NET "DEBUG<3>"		LOC = "P119";
NET "DEBUG<4>"		LOC = "P120";
NET "DEBUG<5>"		LOC = "P121";
#NET ""				LOC = "P124"; # NOTUSED124H
#NET ""				LOC = "P125"; # NOTUSED125H
#NET ""				LOC = "P126"; # NOTUSED126H
NET "DEBUG<6>"		LOC = "P128";
NET "DEBUG<7>"		LOC = "P129";
NET "DEBUG<8>"		LOC = "P130";
NET "DEBUG<9>"		LOC = "P131";
NET "DEBUG<10>"	LOC = "P132";
NET "DEBUG<11>"	LOC = "P133";
NET "DEBUG<12>"	LOC = "P134";
NET "DEBUG<13>"	LOC = "P135";
NET "DEBUG<14>"	LOC = "P136";
NET "DEBUG<15>"	LOC = "P137";
#NET ""				LOC = "P138"; # NOTUSED138H
#NET ""				LOC = "P139"; # NOTUSED139H
#NET ""				LOC = "P140"; # NOTUSED140H
#NET ""				LOC = "P142"; # NOTUSED142H
NET "Z_NIORST"		LOC = "P143";

NET "I_PCICLK2" TNM_NET = I_PCICLK2;
TIMESPEC TS_I_PCICLK2 = PERIOD "I_PCICLK2" 33 MHz HIGH 50%;

INST "I_33M" TNM = TNM_PG_I_CLK;
INST "I_PCICLK" TNM = TNM_PG_P_CLKS;
INST "P_CLKOUT*" TNM = TNM_PG_P_CLKS;
TIMESPEC TS_I_33M_P_CLKS = FROM "TNM_PG_I_CLK" TO "TNM_PG_P_CLKS" 10ns;

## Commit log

2024-02-25 Updated production files
2024-06-24 Added pad-to-pad constraint to synchronize all PCI clocks
2024-06-24 Fix copy&paste-related bugs
